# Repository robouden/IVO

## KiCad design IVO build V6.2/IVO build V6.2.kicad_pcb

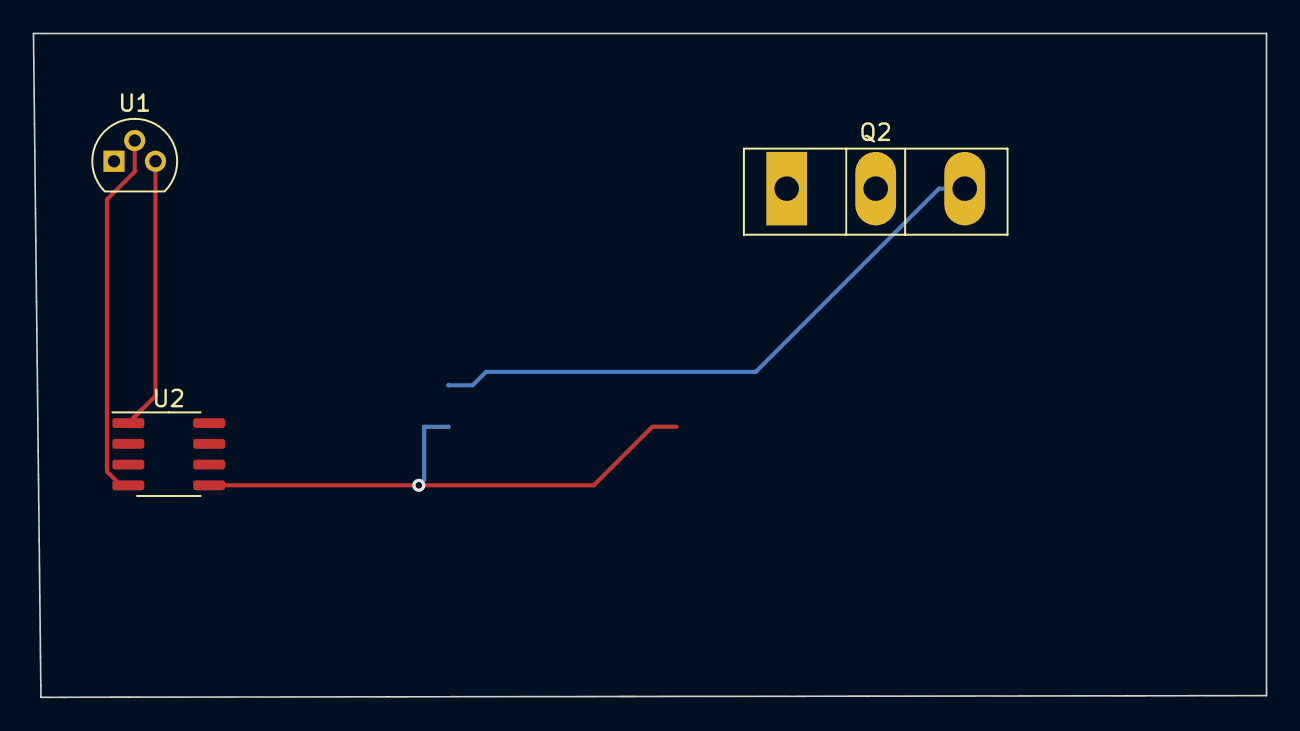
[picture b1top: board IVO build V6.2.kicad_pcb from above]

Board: 2 copper layers, 75.5 x 40.6 mm, 4 parts (1 on the bottom side), 4 nets.

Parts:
Q2: C2M0080120D; TO-247-3_Vertical
U1: L7805; TO-92
U2: 1EDI60I12AF; SOIC-8_3.9x4.9mm_P1.27mm
U3: MGJ1D121505MPC-R7; MGJ1_MUR

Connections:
GND: U1.2 (GND), U2.4 (GND1)
unnamed: Q2.3 (S), U3.6 (0V)
unnamed: U1.3 (OUT), U2.1 (VCC1)
unnamed: U2.5 (VCC2), U3.5 (+VOUT)

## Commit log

2023-11-16 Init
2023-11-16 Added workspace
2023-11-20 Updated schematic
2024-01-25 updated schematic and added picture
2024-05-21 Added docs
2025-01-08 added function generator esp32 and M5stackCode
2025-01-08 Added display control for M5StackCore grey
2025-01-08 added .gitingnore
2025-01-08 Checked duty and frequency changes
2025-01-08 added buttons
2025-01-09 Added Button B
2025-01-10 Good working version
2025-01-10 Good working with long press for frequency changes
